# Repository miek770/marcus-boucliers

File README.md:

# Marcus - Circuit standard des boucliers

## 1. Améliorations pour la prochaine version

1. Ajouter des points de tests pour le raccordement facile d'un oscilloscope;
2. Ajouter un bornier de programmation pour le PIC avec le PICkit2;
3. Inverser la masse et le 5V sur le bouton de réinitialisation, et s'assurer que tous les signaux sont raccordés;
4. Inverser les interrupteurs DIP pour la programmation des points de vie;
5. À partir de maintenant, toujours indiquer les alimentations sur la couche de texte. Sur les autres borniers, indiquer la borne 1 et les masses.

### 1.1 Améliorations optionnelles, à considérer

1. Peut-être ajouter une LED verte pour indiquer que le robot est encore en vie, quitte à mettre un mini-bornier pour un cavalier. Mais c'est vraiment optionnel, à valider;
2. Remplacer les sorties digitales non-essentielles (information) par un port de communication I2C;
3. Faire un format de PCB pouvant être empilé avec le BBB.

## 2. Caractéristiques techniques

- Tension d'alimentation
  - Minimal : 5Vcc
  - Maximal : 6Vcc
- Niveau logique
  - 0-5 Vcc (TTL)
- Temps de réaction
  - À compléter
- Fréquence : 4MHz

## 3. Borniers d'interface

- TB0 : Alimentation
  - 1. Gnd
  - 2. 5V
- TB1 : Interface contrôleur
  - 1. Mort
  - 2. Bouclier 1
  - 3. Bouclier 2
  - 4. Bouclier 3
  - 5. Bouclier 4
  - 6. Réinitialise
  - 7. RB7
  - 8. Gnd
- TB2 : Interface boucliers
  - 1. Bouclier 1
  - 2. Gnd
  - 3. Bouclier 2
  - 4. Gnd
  - 5. Bouclier 3
  - 6. Gnd
  - 7. Bouclier 4
  - 8. Gnd

### 3.1 TB0 – Alimentation

Ce bornier sert à fournir une alimentation régulée à l'externe à une tension entre 5 et 6 VCC. Il n'y a aucun régulateur de tension ni condensateur régulateur dans le circuit standard des boucliers. La masse doit être isolée des composants de puissance afin d'éviter de perturber le fonctionnement des composants sensibles du circuit.

### 3.2 TB1 – Interface contrôleur

L'interface contrôleur sert à communiquer de l'information sur l'état des boucliers au contrôleur principal, et à recevoir des commandes de réinitialisation une fois que les données ont bien été communiquées.

#### 3.2.1 Sorties

Les bornes 3 à 7, c'est-à-dire « Mort », « Bouclier 1 », « Bouclier 2 », « Bouclier 3 » et « Bouclier 4 » servent à communiquer l'état des boucliers, ainsi que le statut de mort (voir section 4). La sortie « Mort » est normalement à 0 et passe à 1 (voir section 2) lorsque les points de vies ont été épuisés (voir section 4). Après que la sortie soit passée à 1, une réinitialisation manuelle […] ou une coupure de l'alimentation V+ est requise afin de remettre le compteur de vies à sa valeur initiale et remettre la sortie de mort à 0. Les sorties « Bouclier 1 », « Bouclier 2 », « Bouclier 3 » et « Bouclier 4 » sont normalement à 0 et passent à 1 (voir section 2) lorsqu'un impact réussi […] est détecté sur le bouclier correspondant. La sortie en question est maintenue à 1 jusqu'à la prochaine réinitialisation logicielle (voir section 3.2.2). Il est important de noter que la réinitialisation des sorties 4 à 7 n'a aucun effet sur le décompte des impacts, et donc le statut de mort.

#### 3.2.2 Entrée

La borne 8 « Réinitialisation » sert à ramener l'état des sorties 4 à 7 (voir section 3.2.1) à 0, soit leur état au repos. Elle est activée par un 1 logique et n'a aucun effet sur le décompte des impacts ni le statut de mort. Elle est à la disposition du concepteur, pour information, dans le cas où il voudrait inclure l'état des boucliers à sa logique.

#### 3.2.3 RB7

La borne RB7 est actuellement non-utilisée, mais raccordée au signal RB7 du PIC.

### 3.3 TB2 – Interface boucliers

Raccordement des capteurs LDT0 de MEAS (numéro de matériel 0-1002794-1, voir note d'application 111398). Le LM324N alimenté à 0-5V agit comme un redresseur simple alternance, avec un filtre passe-bas ayant une fréquence de coupure de 1/(2*pi*C*R2) = 8Hz, et un gain 1+R2/R1 = 21 à 0Hz. Le signal résultant vers le PIC est donc une belle courbe de détection lissée. Il reste à tester la réponse sur le montage final et à ajuster le gain, au besoin.

Le LDT0 devrait être utilisé comme capteur de vibration, il est donc possible que le gain doive être augmenté considérablement lorsqu'il sera monté sur son bouclier. Une autre solution serait de faire un bouclier flexible et léger et de le fixer sur le capteur lui-même.

En résumé, il reste des tests à faire mais il faudra simplement ajuster les 2 résistances et le condensateur de chaque circuit.

## 4. Points de vie

Les points de vie, à l'état initial, sont définis par la configuration d'un interrupteur DIP à 6 positions alors que le circuit est non-alimenté. Chaque impact détecté abaisse la quantité de points de vie de 1, jusqu'à ce qu'elle atteigne 0. La borne 3 « Mort » passe alors à 1 et le circuit doit être réinitialisé par la méthode décrite en 3.2.1.

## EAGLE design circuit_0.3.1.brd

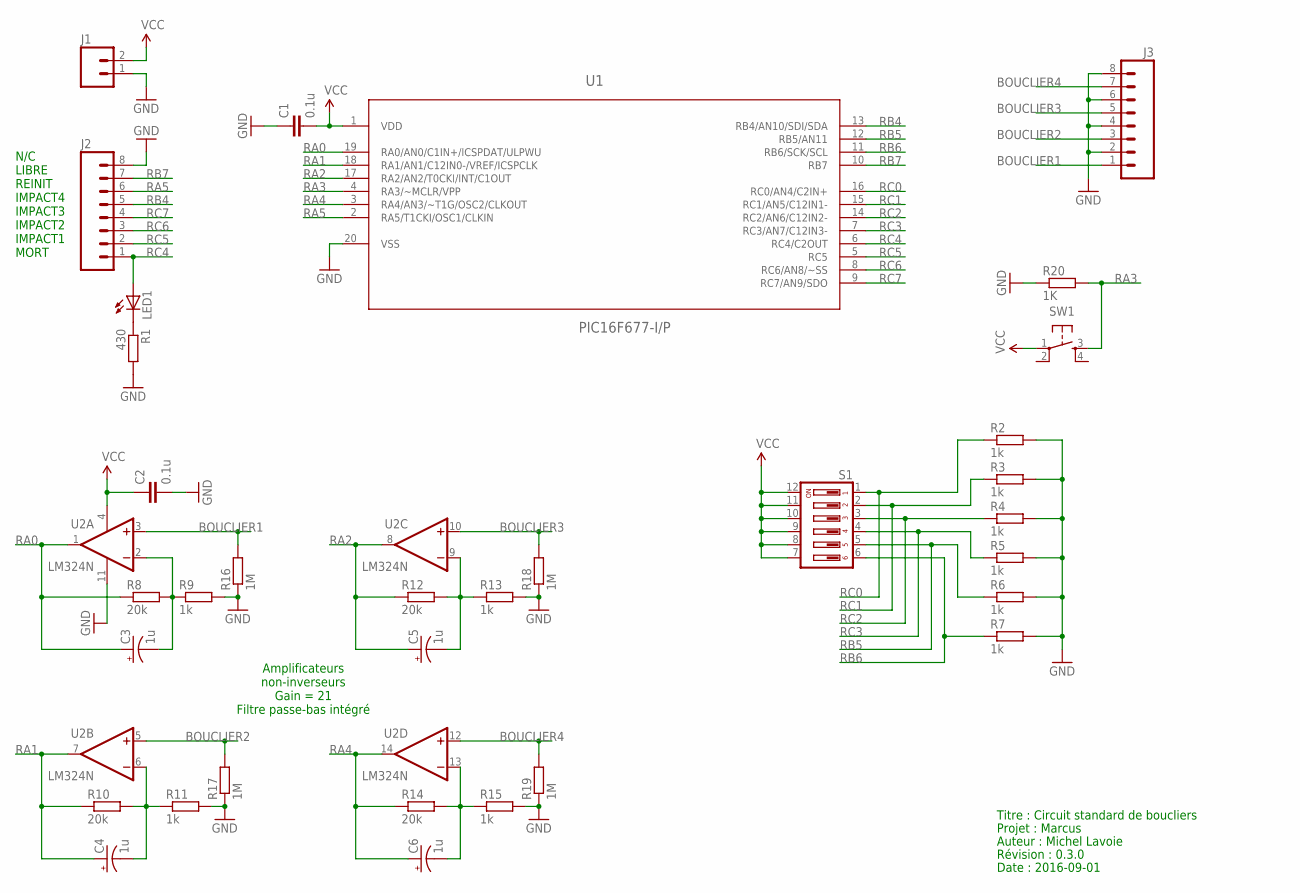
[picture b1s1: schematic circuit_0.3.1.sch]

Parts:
C1, C2: 0.1u; CAP-PTH-SMALL
C3, C4, C5, C6: 1u; E2,5-5
J1: M02PTH; 1X02
J2, J3: M08NO_SILK; 1X08_PIN1_NO_SILK
LED1: LED3MM
R1: 430; 0207/10
R2, R3, R4, R5, R6, R7, R9, R11, R13, R15: 1k; 0207/10
R8, R10, R12, R14: 20k; 0207/10
R16, R17, R18, R19: 1M; 0207/10
R20: 1K; 0207/10
S1: DIP06YL
SW1: TAC_SWITCHPTH; TACTILE-PTH
U1: PIC16F677-I/P; DIP254P762X533-20
U2: LM324N; DIL14

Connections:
BOUCLIER1: J3.1, R16.2, U2.3 (+IN)
BOUCLIER2: J3.3, R17.2, U2.5 (+IN)
BOUCLIER3: J3.5, R18.2, U2.10 (+IN)
BOUCLIER4: J3.7, R19.2, U2.12 (+IN)
GND: C1.1, C2.2, J1.1, J2.8, J3.2, J3.4, J3.6, J3.8, R1.2, R2.2, R3.2, R4.2, R5.2, R6.2, R7.2, R9.2, R11.2, R13.2, R15.2, R16.1, R17.1, R18.1, R19.1, R20.1, U1.20 (VSS), U2.11 (V-)
unnamed: C4.-, R10.2, R11.1, U2.6 (-IN)
unnamed: LED1.K (C), R1.1
unnamed: C3.-, R8.2, R9.1, U2.2 (-IN)
unnamed: C5.-, R12.2, R13.1, U2.9 (-IN)
unnamed: C6.-, R14.2, R15.1, U2.13 (-IN)
RA0: C3.+, R8.1, U1.19 (RA0/AN0/C1IN+/ICSPDAT/ULPWU), U2.1 (OUT)
RA1: C4.+, R10.1, U1.18 (RA1/AN1/C12IN0-/VREF/ICSPCLK), U2.7 (OUT)
RA2: C5.+, R12.1, U1.17 (RA2/AN2/T0CKI/INT/C1OUT), U2.8 (OUT)
RA3: R20.2, SW1.3, U1.4 (RA3/~MCLR/VPP)
RA4: C6.+, R14.1, U1.3 (RA4/AN3/~T1G/OSC2/CLKOUT), U2.14 (OUT)
RA5: J2.6, U1.2 (RA5/T1CKI/OSC1/CLKIN)
RB4: J2.5, U1.13 (RB4/AN10/SDI/SDA)
RB5: R6.1, S1.5, U1.12 (RB5/AN11)
RB6: R7.1, S1.6, U1.11 (RB6/SCK/SCL)
RB7: J2.7, U1.10 (RB7)
RC0: R2.1, S1.1, U1.16 (RC0/AN4/C2IN+)
RC1: R3.1, S1.2, U1.15 (RC1/AN5/C12IN1-)
RC2: R4.1, S1.3, U1.14 (RC2/AN6/C12IN2-)
RC3: R5.1, S1.4, U1.7 (RC3/AN7/C12IN3-)
RC4: J2.1, LED1.A, U1.6 (RC4/C2OUT)
RC5: J2.2, U1.5 (RC5)
RC6: J2.3, U1.8 (RC6/AN8/~SS)
RC7: J2.4, U1.9 (RC7/AN9/SDO)
VCC: C1.2, C2.1, J1.2, S1.7, S1.8, S1.9, S1.10, S1.11, S1.12, SW1.1, U1.1 (VDD), U2.4 (V+)

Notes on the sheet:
N/C LIBRE REINIT IMPACT4 IMPACT3 IMPACT2 IMPACT1 MORT
Titre : Circuit standard de boucliers
Projet : Marcus
Auteur : Michel Lavoie
Révision : 0.3.0
Date : 2016-09-01
Amplificateurs non-inverseurs Gain = 21 Filtre passe-bas intégré

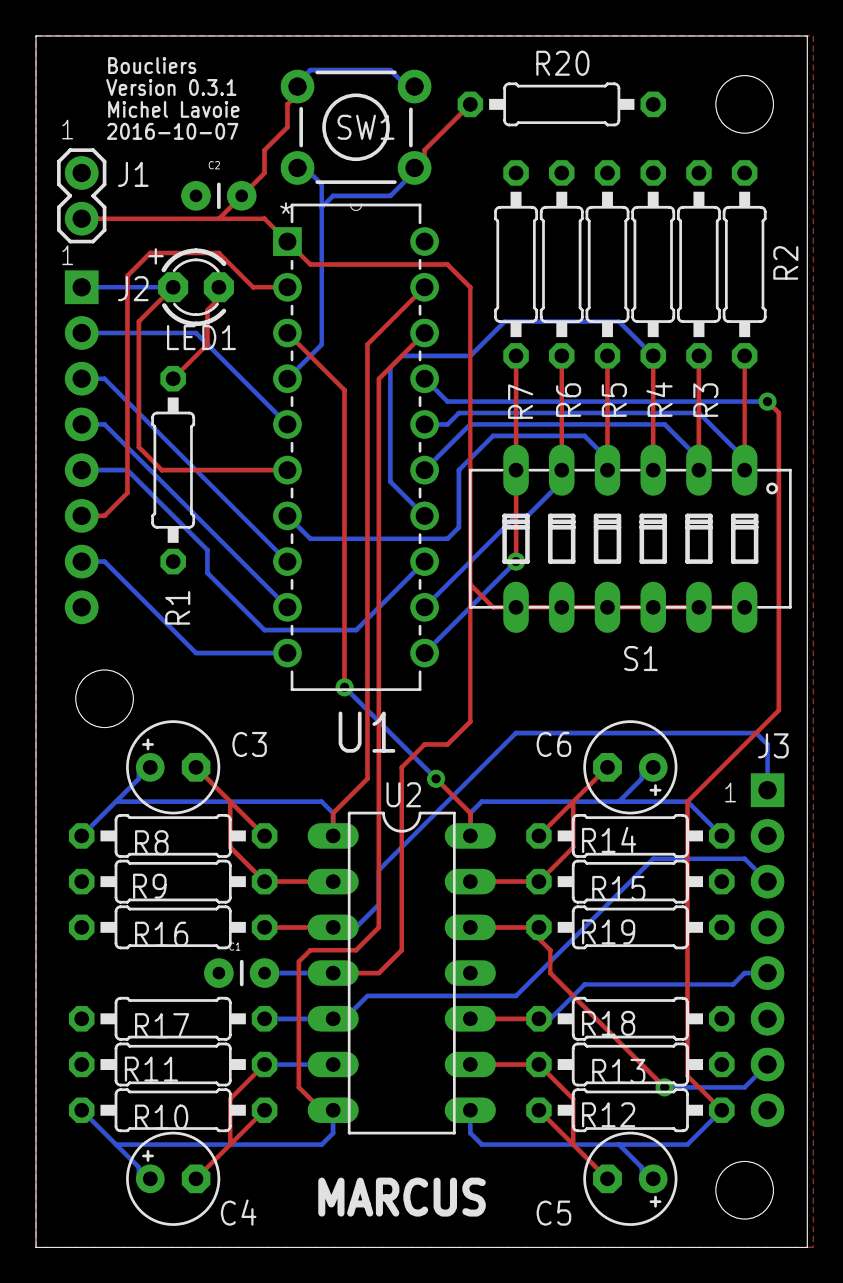
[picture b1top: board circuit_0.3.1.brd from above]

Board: 2 copper layers, 42.9 x 67.3 mm, 34 parts (0 on the bottom side), 29 nets.

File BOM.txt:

Partlist exported from C:/Users/lavoi/Dropbox/Projets/Marcus3/Eagle/projects/Marcus - Boucliers/circuit_0.3.0.sch at 2016-09-02 12:24

Part Value         Device        Package           Description                          
C1   0.1u          CAPPTH        CAP-PTH-SMALL     Capacitor                            
C2   0.1u          CAPPTH        CAP-PTH-SMALL     Capacitor                            
C3   1u            CPOL-USE2.5-5 E2,5-5            POLARIZED CAPACITOR, American symbol 
C4   1u            CPOL-USE2.5-5 E2,5-5            POLARIZED CAPACITOR, American symbol 
C5   1u            CPOL-USE2.5-5 E2,5-5            POLARIZED CAPACITOR, American symbol 
C6   1u            CPOL-USE2.5-5 E2,5-5            POLARIZED CAPACITOR, American symbol 
J1                 M02PTH        1X02              Standard 2-pin 0.1" header. Use with 
J2                 M08NO_SILK    1X08_PIN1_NO_SILK Header 8                             
J3                 M08NO_SILK    1X08_PIN1_NO_SILK Header 8                             
LED1               LED3MM        LED3MM            LED                                  
R1   430           R0207/10      0207/10           RESISTOR, European symbol            
R2   1k            R0207/10      0207/10           RESISTOR, European symbol            
R3   1k            R0207/10      0207/10           RESISTOR, European symbol            
R4   1k            R0207/10      0207/10           RESISTOR, European symbol            
R5   1k            R0207/10      0207/10           RESISTOR, European symbol            
R6   1k            R0207/10      0207/10           RESISTOR, European symbol            
R7   1k            R0207/10      0207/10           RESISTOR, European symbol            
R8   20k           R0207/10      0207/10           RESISTOR, European symbol            
R9   1k            R0207/10      0207/10           RESISTOR, European symbol            
R10  20k           R0207/10      0207/10           RESISTOR, European symbol            
R11  1k            R0207/10      0207/10           RESISTOR, European symbol            
R12  20k           R0207/10      0207/10           RESISTOR, European symbol            
R13  1k            R0207/10      0207/10           RESISTOR, European symbol            
R14  20k           R0207/10      0207/10           RESISTOR, European symbol            
R15  1k            R0207/10      0207/10           RESISTOR, European symbol            
R16  1M            R0207/10      0207/10           RESISTOR, European symbol            
R17  1M            R0207/10      0207/10           RESISTOR, European symbol            
R18  1M            R0207/10      0207/10           RESISTOR, European symbol            
R19  1M            R0207/10      0207/10           RESISTOR, European symbol            
R20  1K            R0207/10      0207/10           RESISTOR, European symbol            
S1                 DIP06YL       DIP06YL           DIL/CODE SWITCH                      
SW1                TAC_SWITCHPTH TACTILE-PTH       Momentary Switch                     
U1   PIC16F677-I/P PIC16F677-I/P DIP254P762X533-20 8 Bit CMOS Microcontrollers          
U2   LM324N        LM324N        DIL14             OP AMP

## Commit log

2016-09-05 Initialisation, après commande du PCB.
2016-09-05 Effacé les révision précédentes.
2016-09-05 Ajouté programmation du PIC sur MPLAB.
2016-09-05 Effacé BOM qui n'était pas à jour de toute façon.
2016-09-23 Nouvelle image.
2016-10-29 Circuit 0.3.1 fonctionnel avec code PIC.
2016-10-29 Nettoyé le code, effacé la version 0.3.0.
2016-10-30 Ajout sections et améliorations.
2016-10-30 Correction des masses (Gnd).
2016-11-05 Ajouté tab requis, enlevé adresse MAIN_PROG
2016-11-05 Détails mineurs.
2016-12-11 Added some pictures.
2016-12-16 Changé le titre du document.

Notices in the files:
parts and their libraries:
SparkFun-Capacitors: Licensing: Creative Commons ShareAlike 4.0 International - https://creativecommons.org/licenses/by-sa/4.0
